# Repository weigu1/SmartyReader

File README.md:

# SmartyReader: Reading encrypted Luxembourgish smartmeter data

## All infos on: <http://weigu.lu/microcontroller/smartyReader/index.html>

## Some infos

Because of the EU Energy Efficiency Directive from 2012 the gas and electricity Distribution System Operators (DSO) in Luxembourg replaced there gas and energy meters with smartmeters (named smarty :() from Sagemcom (T210-D).

As it seems the same smartmeters are deployed in Sweden, parts of Austria and the Netherlands.

These smartmeters have a user port that delivers 10 second data (RJ12 connector under the green lid). The P1 data output communication protocol and format is specified in the  [Dutch Smart Meter Requirements v5.0.2 ](https://smarty.creos.net/wp-content/uploads/DutchSmartMeterRequirements.pdf). The solution deployed in Luxembourg includes an additional security layer standard that is conform to the IDIS package 2.0 requirement. The encryption layer is based on DLMS security suite 0 algorithm: AES128-GCM. More information can be found in this [document](https://smarty.creos.net/wp-content/uploads/P1PortSpecification.pdf).

The Smartyreader is a simple board designed with KiCAD and decrypting the smartmeter data with an ESP8266 (Lolin D1 mini pro). The data is then published over MQTT via WiFi or Ethernet. A new version allows also to use LoRa or LoRaWAN.

For infos from the newest software look here: <https://github.com/weigu1/SmartyReader/tree/main/Arduino/SmartyReader_P1_WiFi_Ethernet>.

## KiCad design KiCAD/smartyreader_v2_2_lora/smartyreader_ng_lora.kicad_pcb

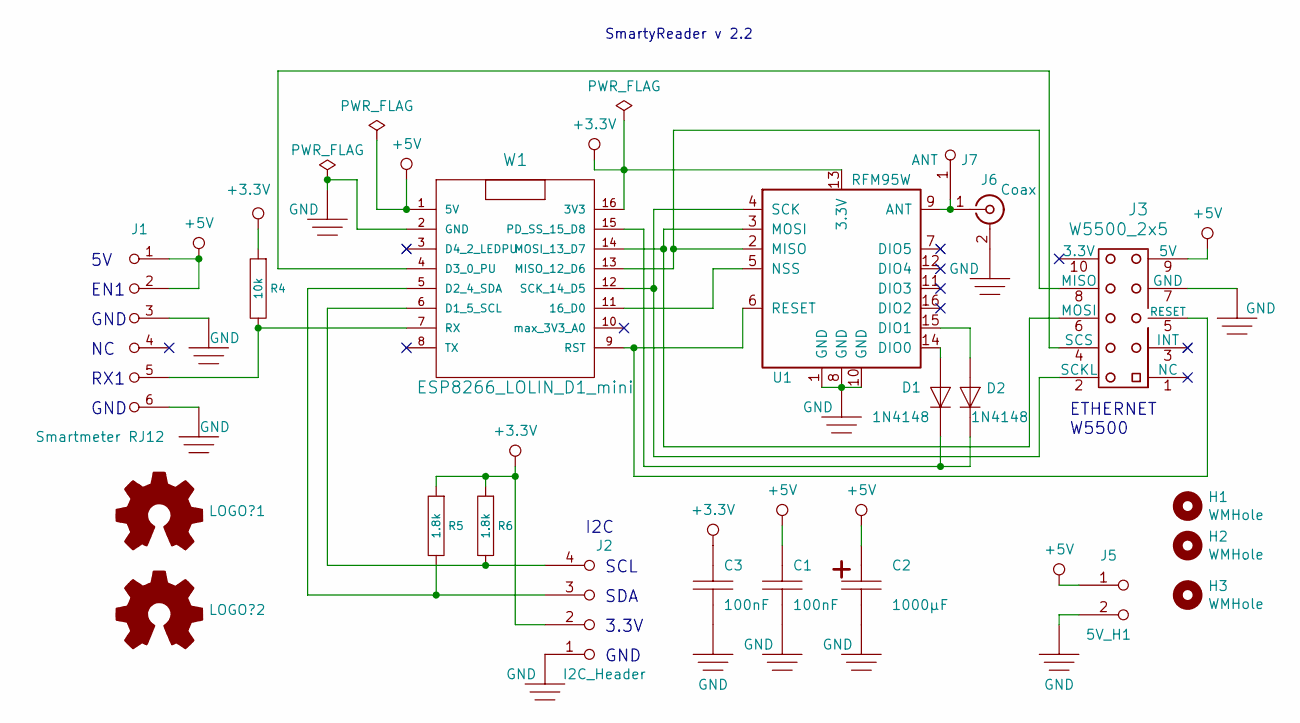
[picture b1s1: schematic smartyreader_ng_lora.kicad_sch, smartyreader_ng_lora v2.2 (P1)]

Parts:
C1, C3: 100nF; WC1
C2: 1000µF; WC1V
D1, D2: 1N4148; W0805
H1, H2, H3: WMHole; WPin_3mm
J1: Smartmeter RJ12; WRJ12
J2: I2C_Header; WSIL4_SL
J3: W5500_2x5; WW5500
J5: 5V_H1; WSIL2_SL
J6: Coax; U.FL_Molex_MCRF_73412-0110_Vertical
J7: ANT; WPin_1mm
LOGO?1, LOGO?2: Open_Hardware_Logo; OSHW-Logo_5.7x6mm_SilkScreen
R4: 10k; WR4
R5, R6: 1.8k; W0805
U1: RFM95W; HOPERF_RFM9XW_SMD
W1: ESP8266_LOLIN_D1_mini; WWEMOSD1

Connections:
+3.3V: C3.1, J2.2 (12), R4.1, R5.1, R6.1, U1.13 (3.3V), W1.16 (3V3)
+5V: C1.1, C2.1, J1.1, J1.2, J3.9 (5V), J5.1 (11), W1.1 (5V)
unnamed: D1.1 (A), U1.14 (DIO0)
unnamed: D1.2 (K), D2.2 (K), W1.15 (PD_SS_15_D8)
unnamed: D2.1 (A), U1.15 (DIO1)
unnamed: J1.5, R4.2, W1.7 (RX)
unnamed: J2.3 (13), R5.2, W1.5 (D2_4_SDA)
unnamed: J2.4 (14), R6.2, W1.6 (D1_5_SCL)
unnamed: J3.2 (SCKL), U1.4 (SCK), W1.12 (SCK_14_D5)
unnamed: J3.4 (SCS), W1.4 (D3_0_PU)
unnamed: J3.5 (RESET), U1.6 (RESET), W1.9 (RST)
unnamed: J3.6 (MOSI), U1.3 (MOSI), W1.14 (MOSI_13_D7)
unnamed: J3.8 (MISO), U1.2 (MISO), W1.13 (MISO_12_D6)
unnamed: J6.1 (In), J7.1 (11), U1.9 (ANT)
unnamed: U1.5 (NSS), W1.11 (16_D0)
~: C1.2, C2.2, C3.2, J1.3, J1.6, J2.1 (11), J3.7 (GND), J5.2 (12), J6.2 (Ext), U1.1 (GND), U1.8 (GND), U1.10 (GND), W1.2 (GND)

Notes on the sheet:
EN1
SCL
GND
SDA
SmartyReader v 2.2
ETHERNET W5500
3.3V
I2C
RX1

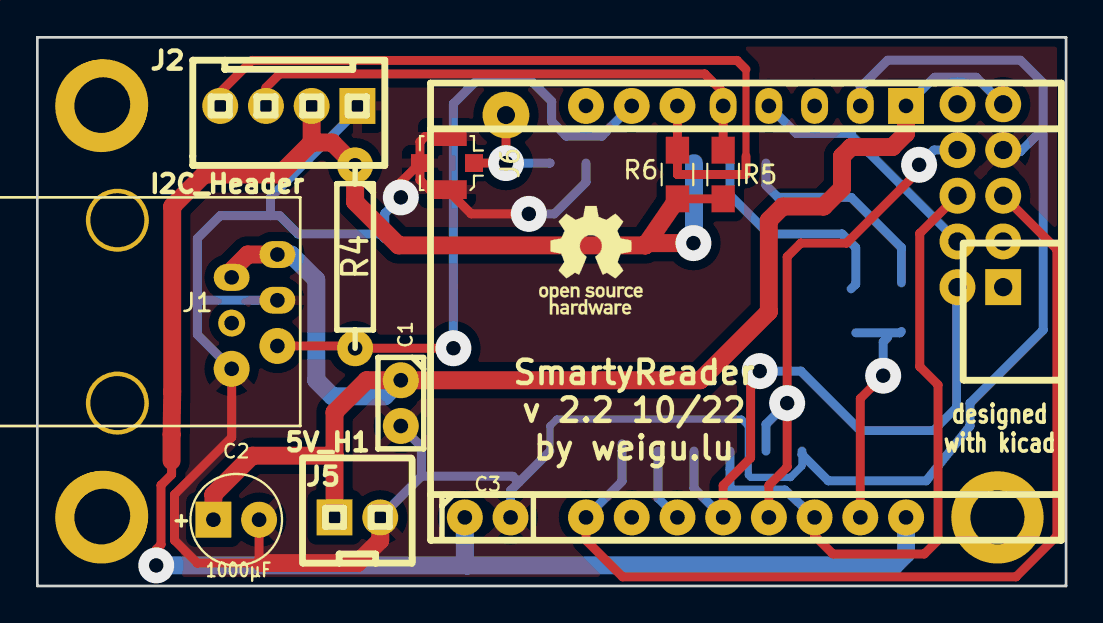
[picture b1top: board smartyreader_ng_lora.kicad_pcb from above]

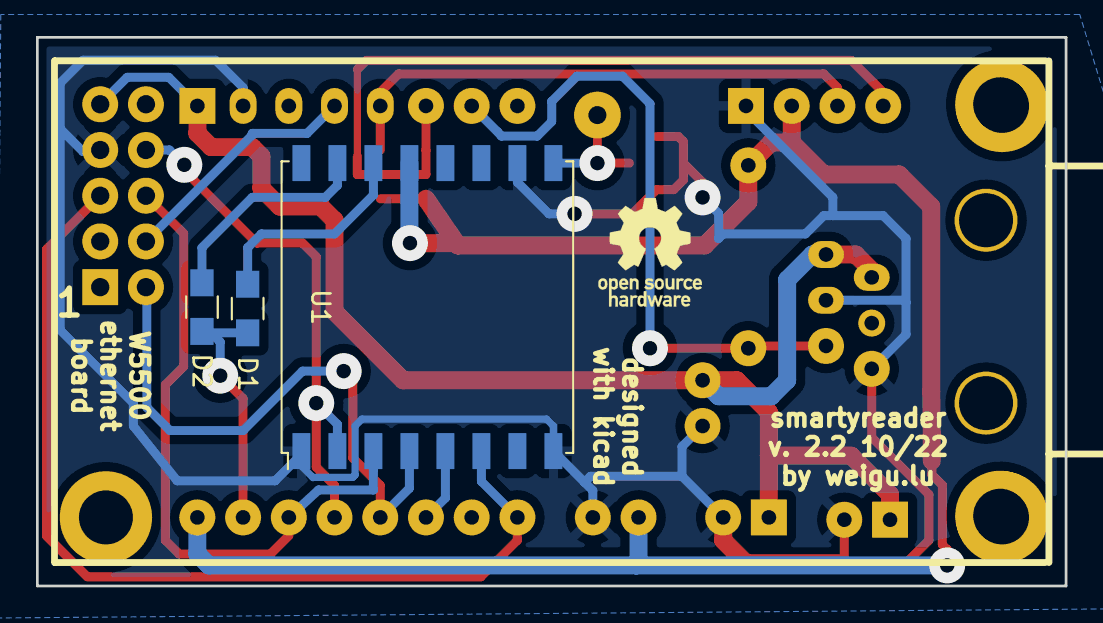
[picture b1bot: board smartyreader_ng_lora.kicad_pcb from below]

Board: 2 copper layers, 57.1 x 30.5 mm, 21 parts (5 on the bottom side), 16 nets.

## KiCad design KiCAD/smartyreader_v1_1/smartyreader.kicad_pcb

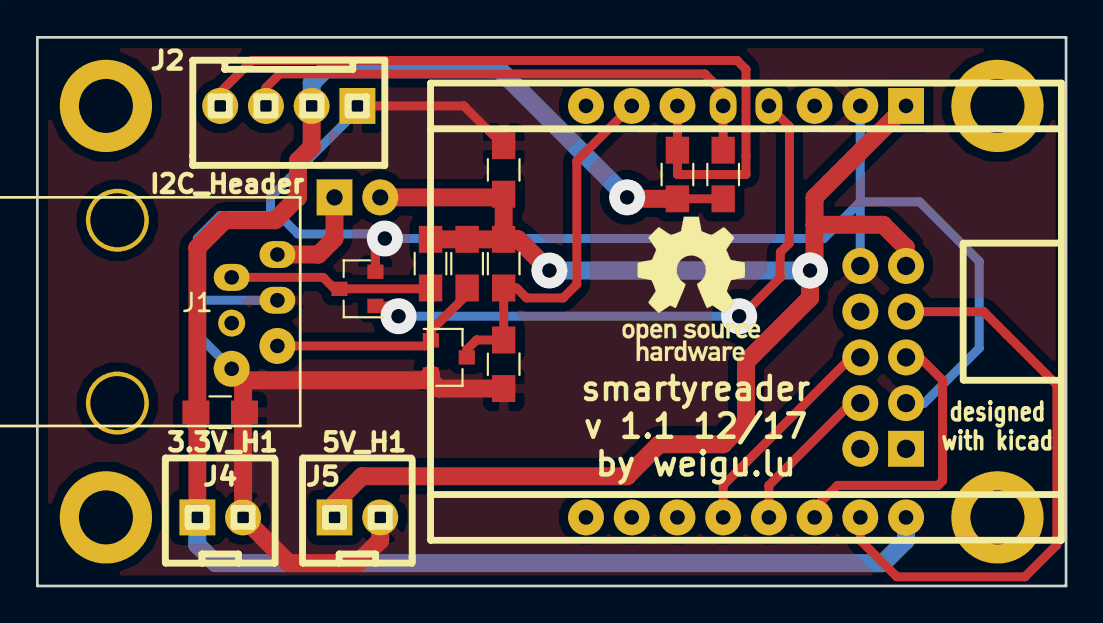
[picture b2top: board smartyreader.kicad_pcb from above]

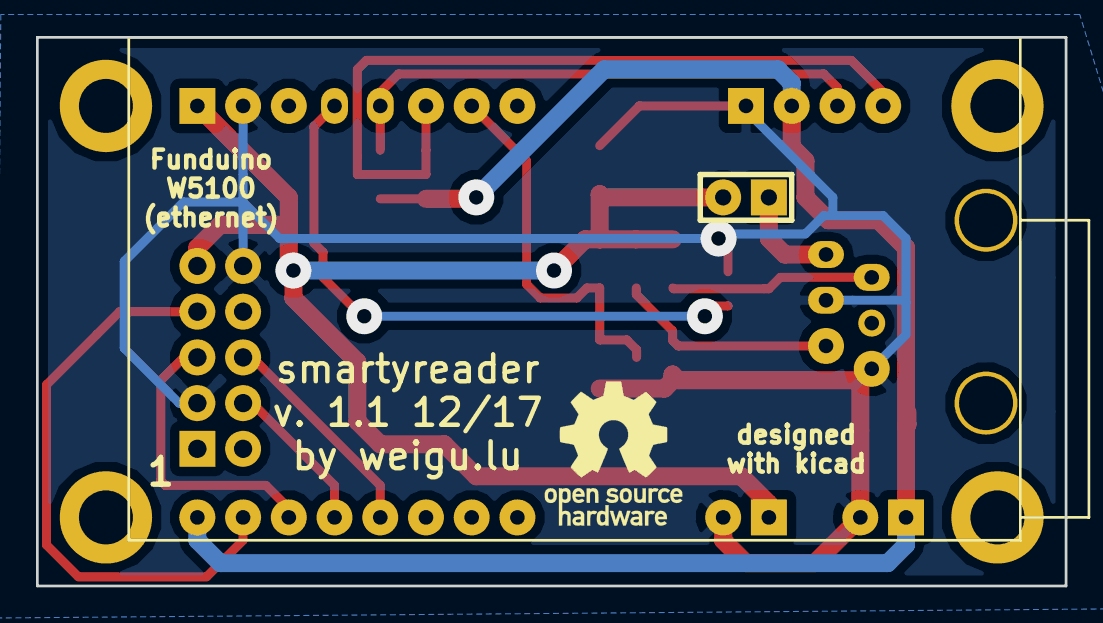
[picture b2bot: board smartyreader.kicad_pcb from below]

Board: 2 copper layers, 57.1 x 30.5 mm, 21 parts (2 on the bottom side), 14 nets.

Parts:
AD1, AD1#2, AD1#3, AD1#4: C1; WPin_3mm
C1, C2: 100n; W0805
J1: RJ12; WRJ12
J2: I2C_Header; WSIL4_SL
J3: W5100_2x5; WW5100
J4: 3.3V_H1; WSIL2_SL
J5: 5V_H1; WSIL2_SL
JP1: Jump; WSIL2
Q1, Q2: 2N7002; SOT-23
R1: 220; W0805
R2: 1k; W0805
R3: 10k; W0805
R4: 15k; W0805
R5, R6: 1.8k; W0805
W1: WEMOS_D1_mini; WWEMOSD1

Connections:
+3.3V: C2.1, J2.2, J4.1, R5.1, R6.1, W1.16
+5V: C1.1, J3.9, J5.1, JP1.2, R1.1, R2.1, R3.1, W1.1
GND: C1.2, C2.2, J1.3, J1.6, J2.1, J3.3, J3.10, J4.2, J5.2, Q1.2, Q2.2, R4.2, W1.2
unnamed: J1.1, JP1.1
unnamed: J1.2, Q1.3, R1.2
unnamed: J1.5, Q2.1, R2.2
unnamed: J2.3, R5.2, W1.5
unnamed: J2.4, R6.2, W1.6
unnamed: J3.4, W1.13
unnamed: J3.5, W1.14
unnamed: J3.6, W1.12
unnamed: J3.7, W1.15
unnamed: Q1.1, W1.4
unnamed: Q2.3, R3.2, R4.1, W1.7

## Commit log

2021-05-03 changed file names
2021-05-03 added PUBLISH_ALL switch
2021-05-04 Auth data now changeable (Greetings to Austria :)
2021-10-11 LoRa Version addes
2022-02-18 corrected links
2022-02-18 Changed image and KiCAD files to V2.1
2022-03-14 added FreeCAD and stl files
2022-03-14 changed comment to publish all in ino
2022-03-17 enhanced housing with notch
2022-03-17 added Readme to FreeCAD folder
2022-04-11 Changed MQTTSECURE to MQTTPASSWORD
2022-04-18 adding calculation of excess power
2022-05-02 one hundred changes ;)
2022-05-02 calculated values also when publishing all
2022-05-17 changed README in /Arduino/SmartyReader_P1_WiFi/
2022-05-24 added gas var type
2022-06-06 Addes BME280 support and NTP time support
2022-06-07 bug in config file, and more infos in the software README
2022-06-12 addes constrain to excess power (no more negative)
2022-07-16 beta to full, changes in ESPToolbox, added Ethernet
2022-10-05 corrected missing fillet
2022-10-15 readded P1 version; corrected kWh to Wh (calc) and added gas_cumul_day
2022-10-25 missing colon
2022-11-19 Support for W5500 Ethernet board (v2.2); KiCAD files (v2.2)
2022-11-19 deletet old Ethernet folder
2023-01-24 changed lin in README
2023-03-31 set enable pin OLD_HARDWARE only in setup()
2023-03-31 no raw debug info
2023-08-28 typo in setup_SR_1.6
2025-04-30 new version 1.7 added
2025-05-06 bug, production instead consumption
2025-05-06 bug, production instead consumption, new last will
2025-05-08 power_from_energy calculated over 1 Minute for better resolution
2025-05-28 added money calculation for exceeding class
2025-09-20 typo
2026-02-19 added 'good to know'
